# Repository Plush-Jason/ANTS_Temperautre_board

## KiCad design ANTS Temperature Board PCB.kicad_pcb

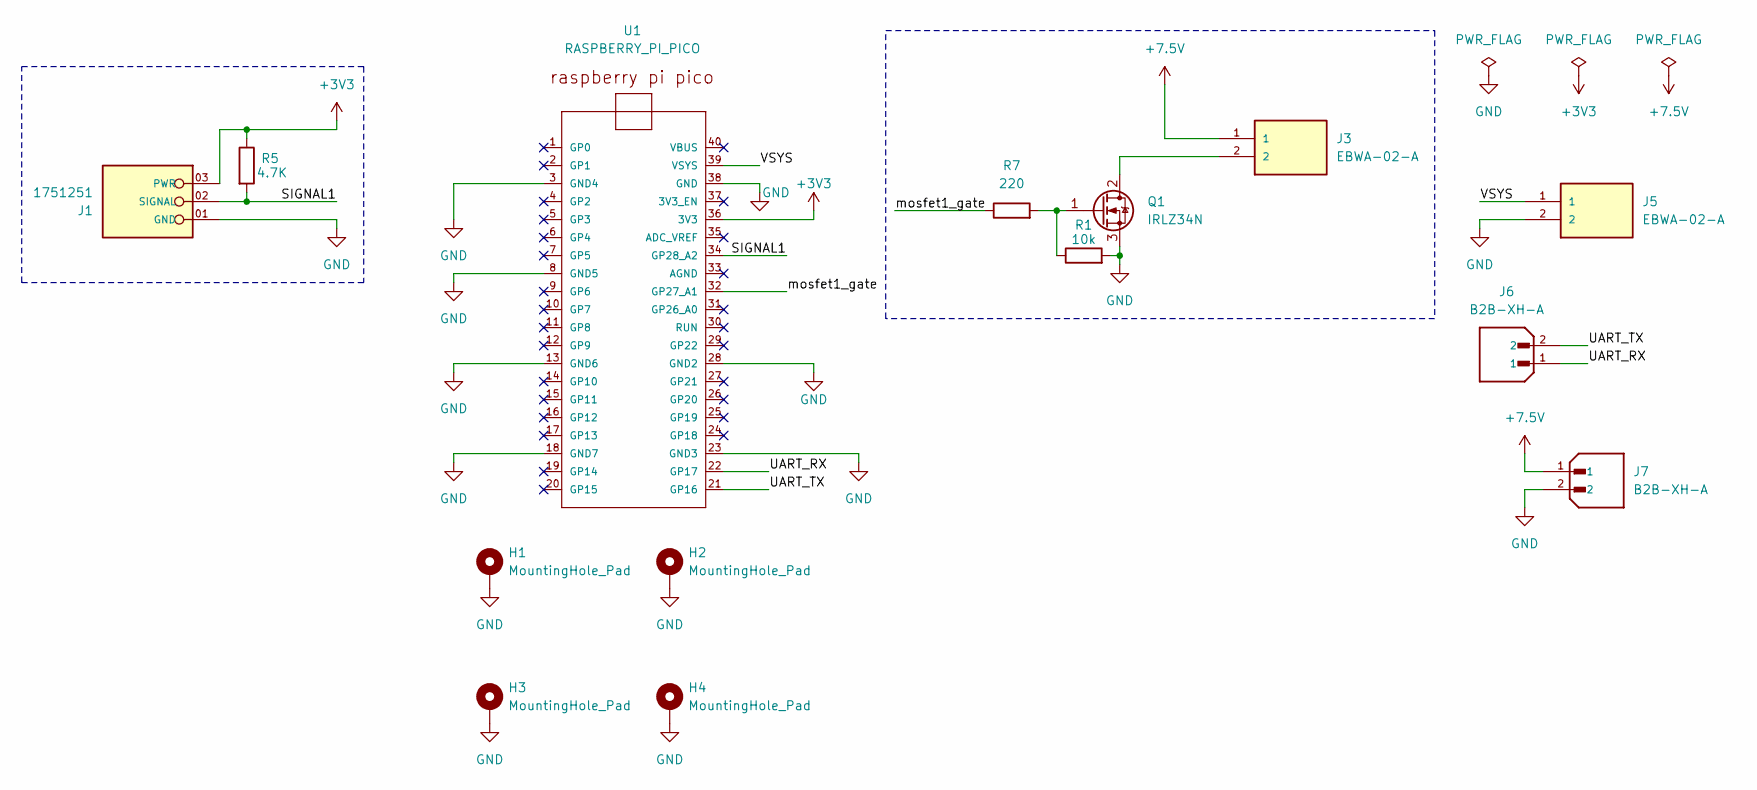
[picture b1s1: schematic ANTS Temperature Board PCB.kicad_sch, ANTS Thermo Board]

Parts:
H1, H2, H3, H4: MountingHole_Pad; MountingHole_2.7mm_M2.5_Pad_Via
J1: 1751251; PHOENIX_1751251; PARTREV 03.03.2021
J3, J5: EBWA-02-A; ADAMTECH_EBWA-02-A; PARTREV A
J6, J7: B2B-XH-A; JST_B2B-XH-A; PARTREV N/A
Q1: IRLZ34N; TO-220-3_Vertical
R1: 10k; R_Axial_DIN0204_L3.6mm_D1.6mm_P7.62mm_Horizontal
R5: 4.7K; R_Axial_DIN0204_L3.6mm_D1.6mm_P7.62mm_Horizontal
R7: 220; R_Axial_DIN0204_L3.6mm_D1.6mm_P7.62mm_Horizontal
U1: RASPBERRY_PI_PICO; RaspberryPi_Pico_Common_THT

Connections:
+3V3: J1.03 (PWR), R5.1, U1.36 (3V3)
+7.5V: J3.1, J7.1
/SIGNAL1: J1.02 (SIGNAL), R5.2, U1.34 (GP28_A2)
/UART_RX: J6.1, U1.22 (GP17)
/UART_TX: J6.2, U1.21 (GP16)
/VSYS: J5.1, U1.39 (VSYS)
/mosfet1_gate: R7.1, U1.32 (GP27_A1)
GND: H1.1 (1_1), H2.1 (1_1), H3.1 (1_1), H4.1 (1_1), J1.01 (GND), J5.2, J7.2, Q1.3 (S), R1.2, U1.3 (GND4), U1.8 (GND5), U1.13 (GND6), U1.18 (GND7), U1.23 (GND3), U1.28 (GND2), U1.38 (GND)
unnamed: J3.2, Q1.2 (D)
unnamed: Q1.1 (G), R1.1, R7.2

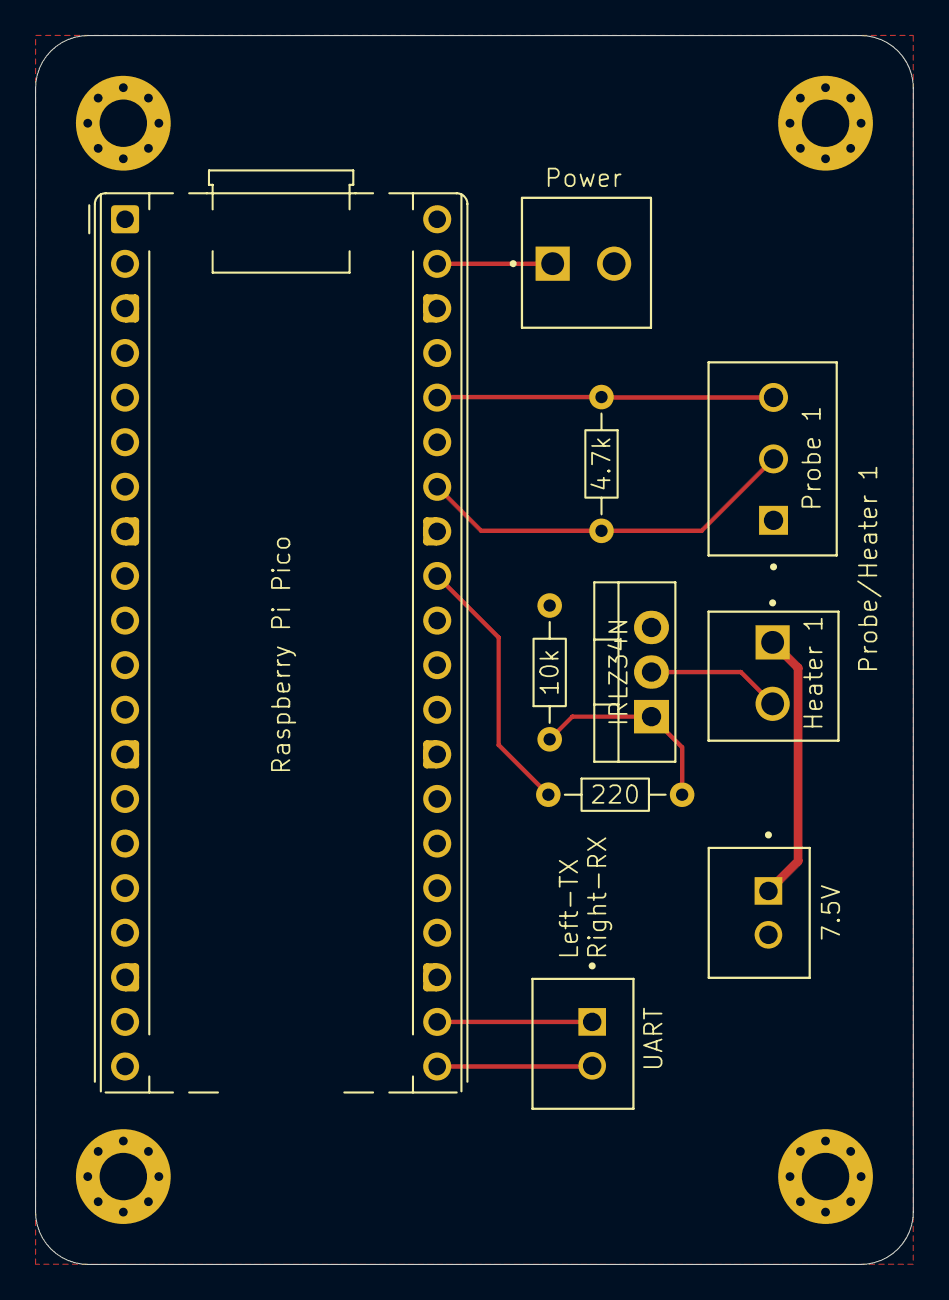
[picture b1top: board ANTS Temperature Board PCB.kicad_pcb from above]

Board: 2 copper layers, 50.0 x 70.0 mm, 14 parts (0 on the bottom side), 10 nets.

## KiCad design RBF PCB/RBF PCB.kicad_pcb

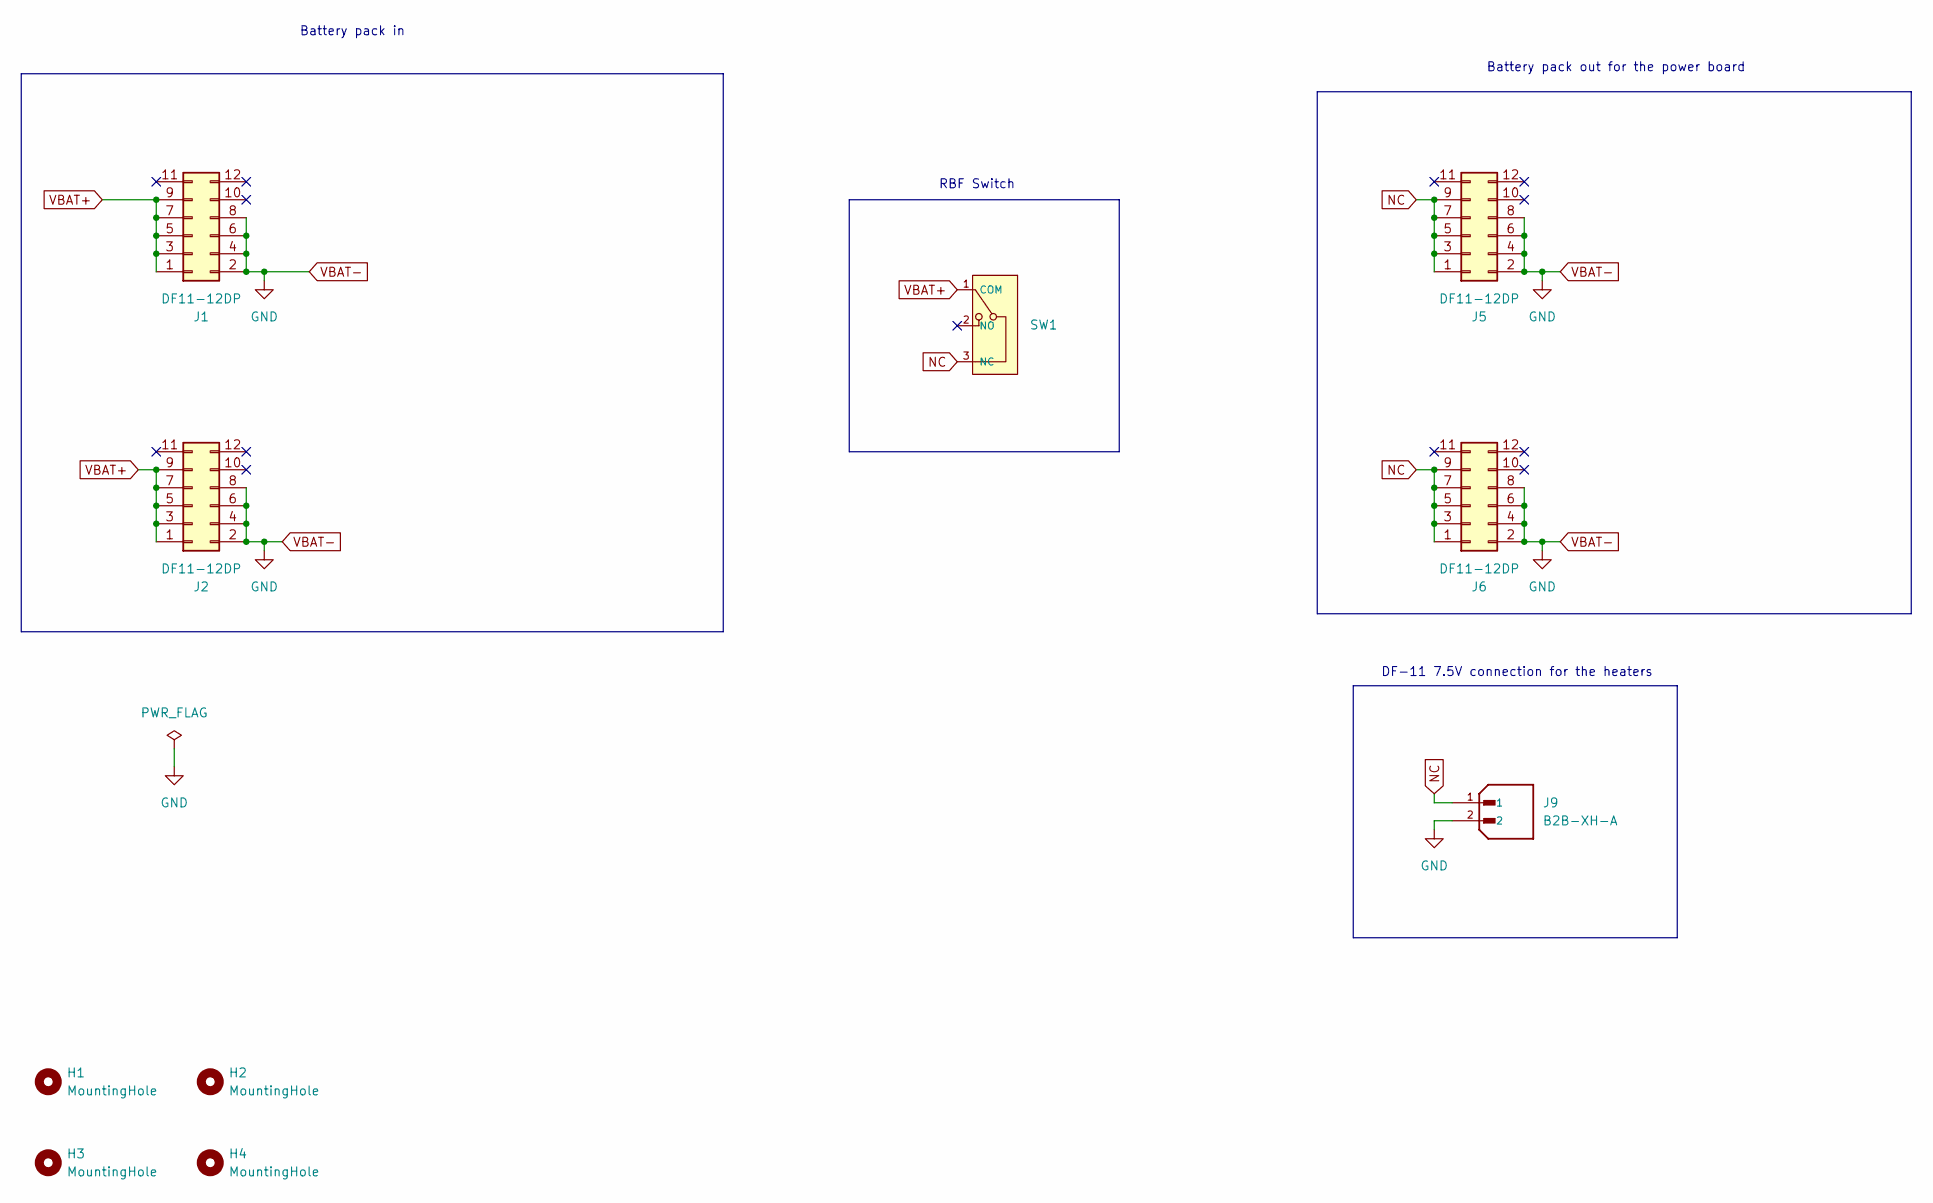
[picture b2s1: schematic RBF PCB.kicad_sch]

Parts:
H1, H2, H3, H4: MountingHole; MountingHole_3.2mm_M3_Pad_Via
J1, J2, J5, J6: DF11-12DP; Hirose_DF11-12DP-2DSA_2x06_P2.00mm_Vertical; LCSC C506658
J9: B2B-XH-A; JST_B2B-XH-A; PARTREV N/A
SW1: RBF Switch foot print

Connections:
NC: J5.1, J5.3, J5.5, J5.7, J5.9, J6.1, J6.3, J6.5, J6.7, J6.9, J9.1, SW1.3 (NC)
VBAT+: J1.1, J1.3, J1.5, J1.7, J1.9, J2.1, J2.3, J2.5, J2.7, J2.9, SW1.1 (COM)
VBAT-: J1.2, J1.4, J1.6, J1.8, J2.2, J2.4, J2.6, J2.8, J5.2, J5.4, J5.6, J5.8, J6.2, J6.4, J6.6, J6.8, J9.2

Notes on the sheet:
DF-11 7.5V connection for the heaters
Battery pack in
Battery pack out for the power board
RBF Switch

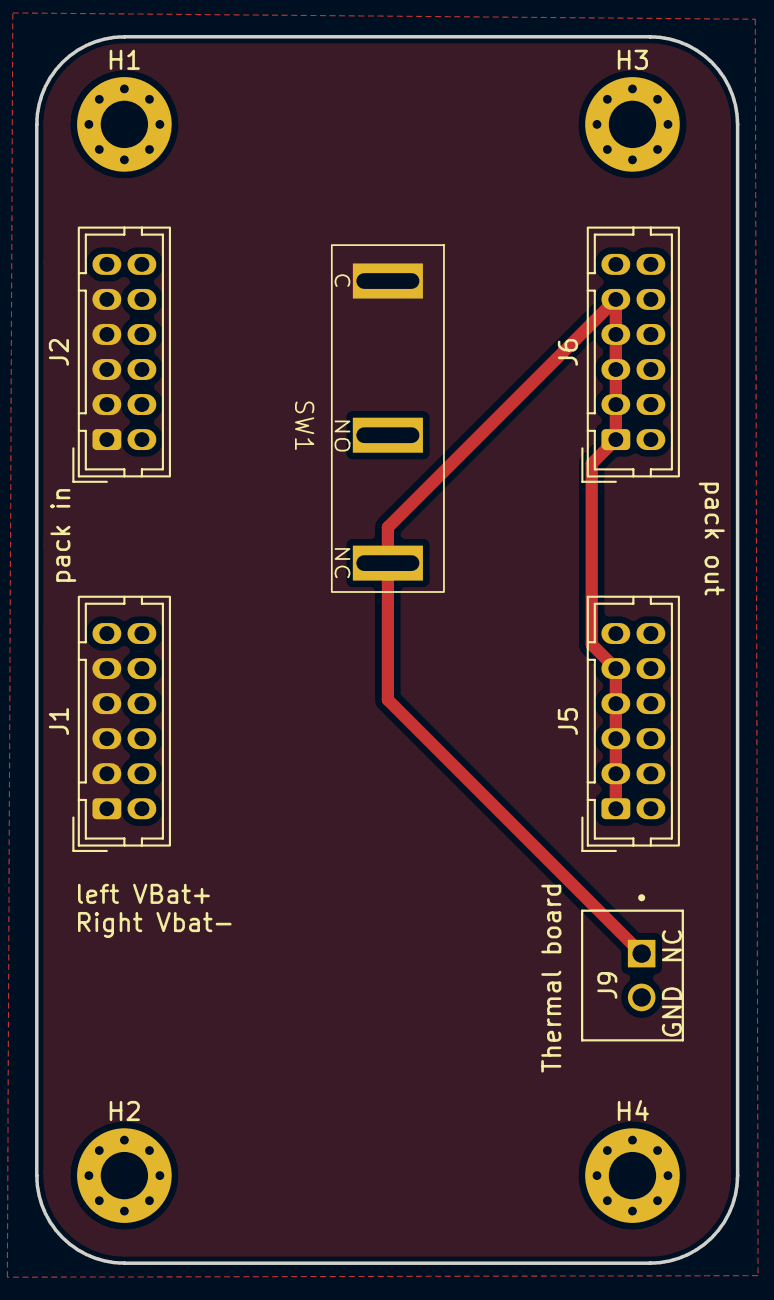
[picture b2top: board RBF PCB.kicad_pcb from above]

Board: 2 copper layers, 40.0 x 70.0 mm, 10 parts (0 on the bottom side), 3 nets.

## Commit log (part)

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2026-06-02 the beginning of JABOB's journey
    creation of the file
